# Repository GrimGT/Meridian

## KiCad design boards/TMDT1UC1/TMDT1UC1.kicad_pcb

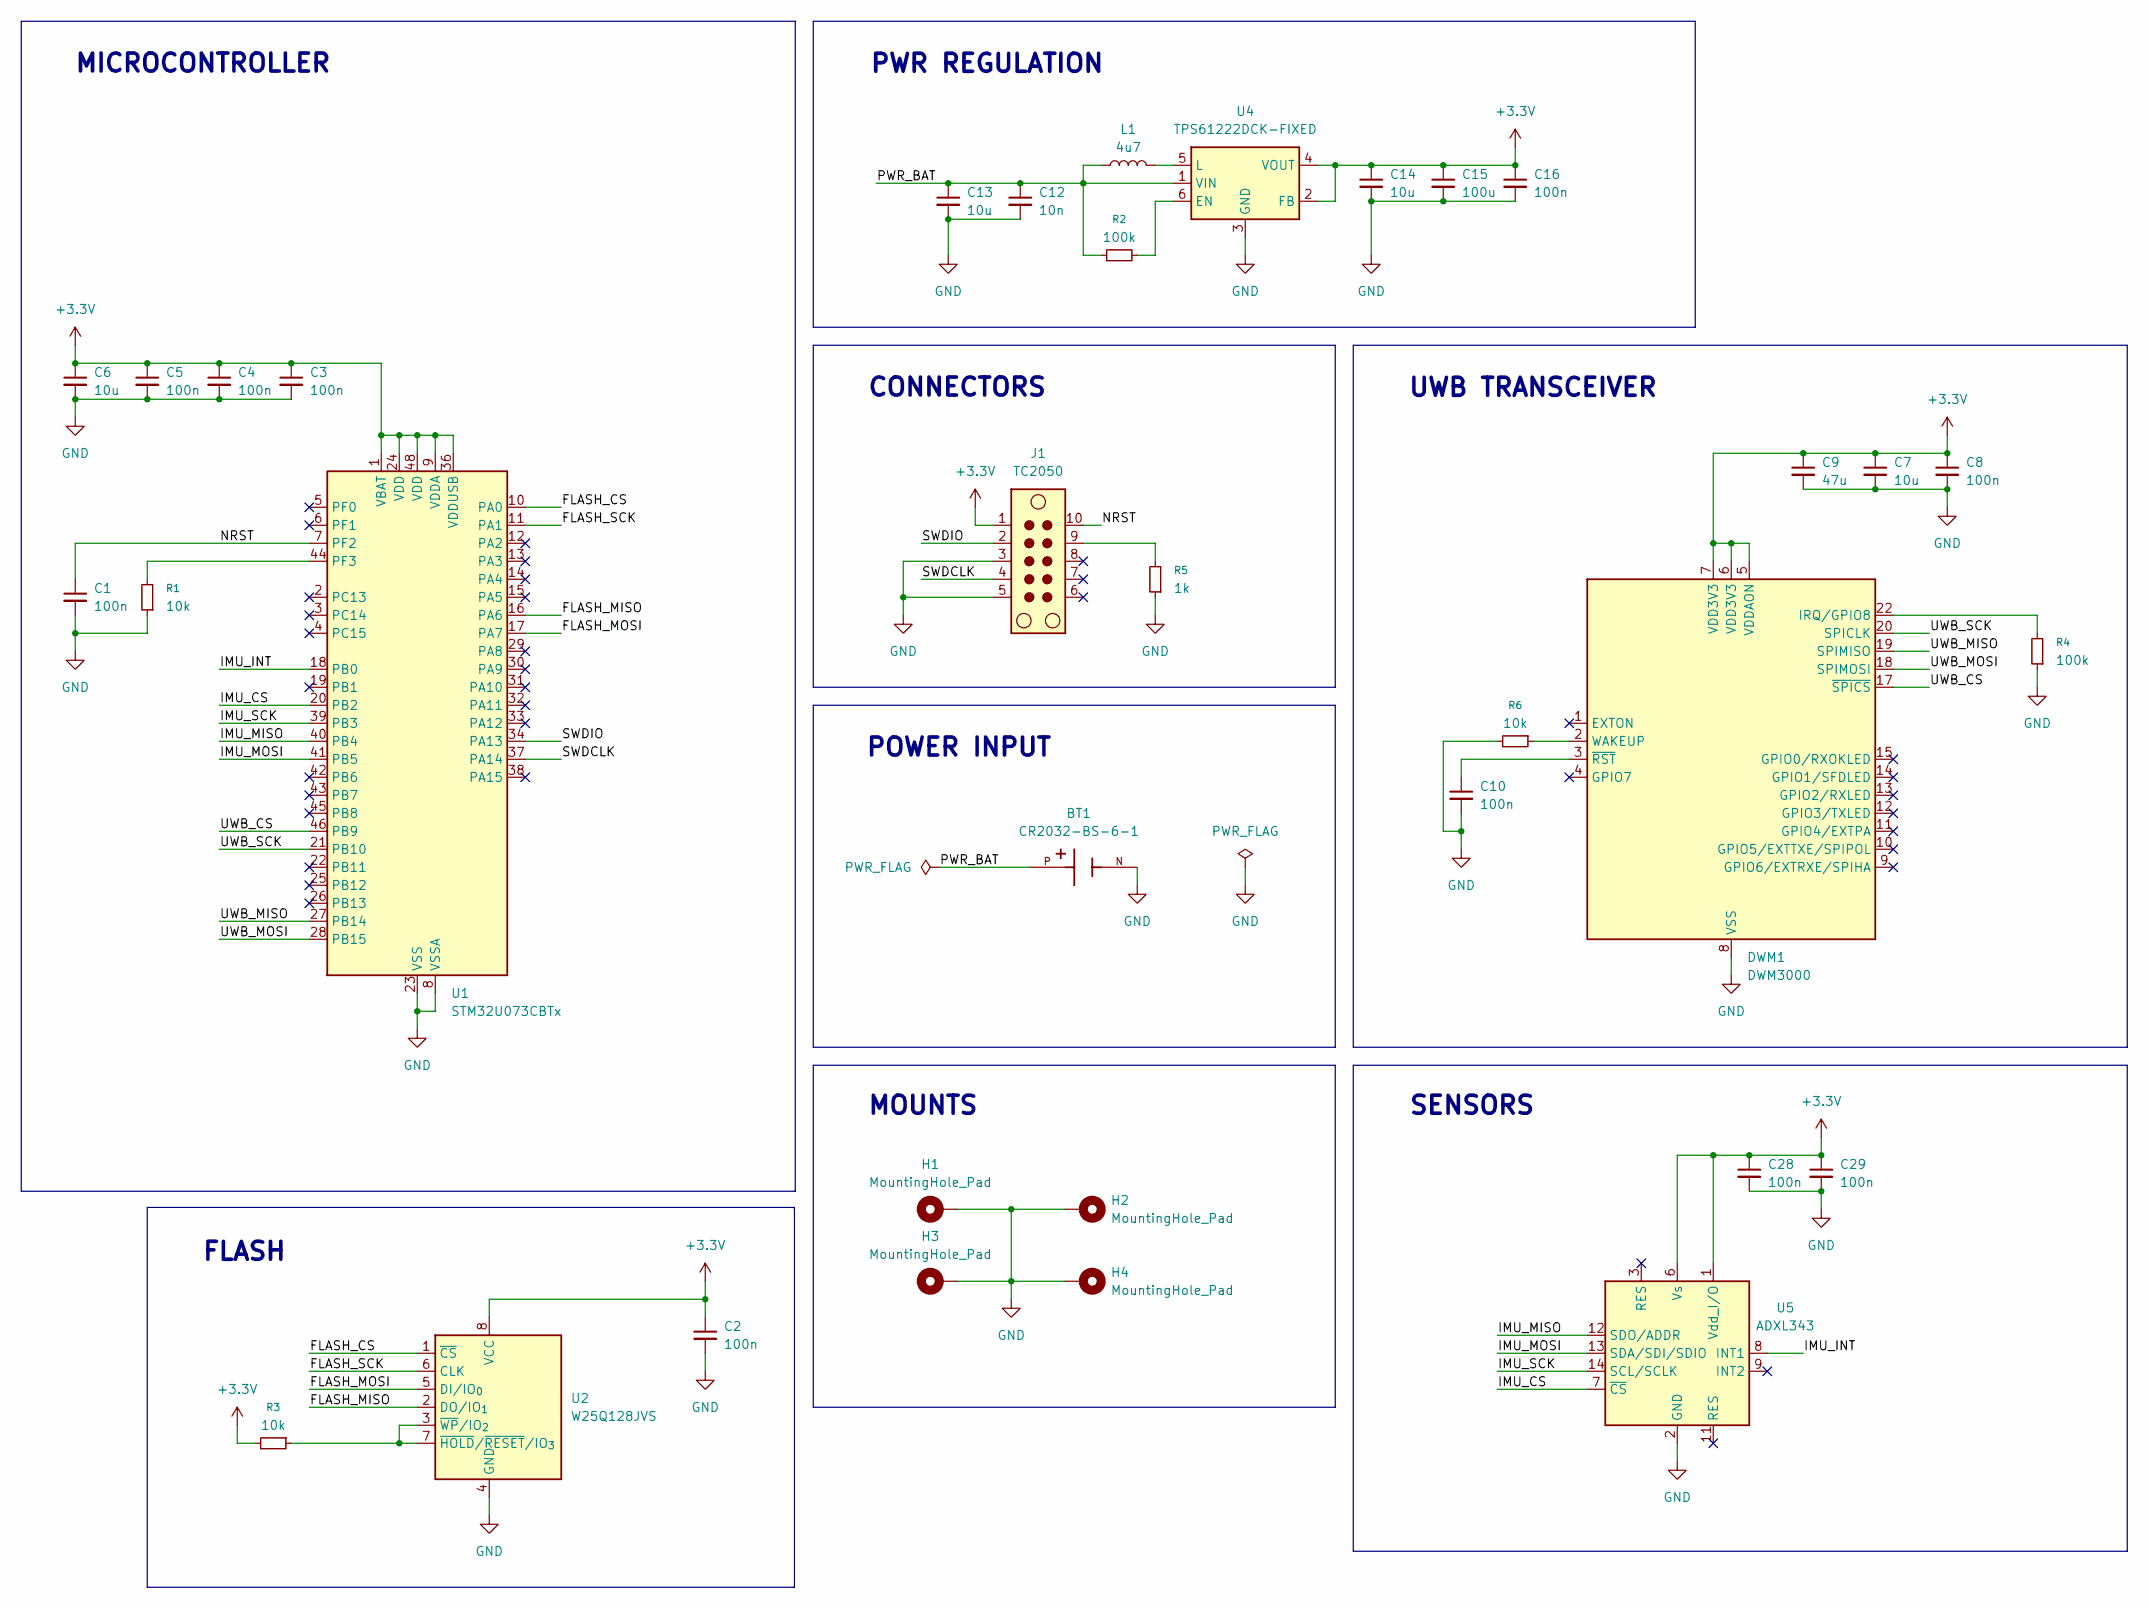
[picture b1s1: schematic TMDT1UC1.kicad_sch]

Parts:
BT1: CR2032-BS-6-1; BAT_CR2032-BS-6-1; PARTREV 2011/2/14
C1, C2, C3, C4, C5, C8, C10, C16, C28, C29: 100n; C_0402_1005Metric
C6, C7, C13, C14: 10u; C_0603_1608Metric
C9: 47u; C_0603_1608Metric
C12: 10n; C_0402_1005Metric
C15: 100u; C_0603_1608Metric
DWM1: DWM3000; DWM1000
H1, H2, H3, H4: MountingHole_Pad; MountingHole_3.2mm_M3_Pad_Via
J1: TC2050; Tag-Connect_TC2050-IDC-NL_2x05_P1.27mm_Vertical
L1: 4u7; L_1210_3225Metric
R1, R3, R6: 10k; R_0402_1005Metric
R2, R4: 100k; R_0402_1005Metric
R5: 1k; R_0402_1005Metric
U1: STM32U073CBTx; LQFP-48_7x7mm_P0.5mm
U2: W25Q128JVS; SOIC-8_5.3x5.3mm_P1.27mm
U4: TPS61222DCK-FIXED; Texas_R-PDSO-G6
U5: ADXL343; LGA-14_3x5mm_P0.8mm_LayoutBorder1x6y

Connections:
+3.3V: C2.1, C3.1, C4.1, C5.1, C6.1, C7.1, C8.1, C9.1, C14.1, C15.1, C16.1, C28.1, C29.1, DWM1.5 (VDDAON), DWM1.6 (VDD3V3), DWM1.7 (VDD3V3), J1.1, R3.2, U1.1 (VBAT), U1.9 (VDDA), U1.24 (VDD), U1.36 (VDDUSB), U1.48 (VDD), U2.8 (VCC), U4.2 (FB), U4.4 (VOUT), U5.1 (Vdd_I/O), U5.6 (Vs)
/FLASH_CS: U1.10 (PA0), U2.1 (~CS)
/FLASH_MISO: U1.16 (PA6), U2.2 (DO/IO_{1})
/FLASH_MOSI: U1.17 (PA7), U2.5 (DI/IO_{0})
/FLASH_SCK: U1.11 (PA1), U2.6 (CLK)
/IMU_CS: U1.20 (PB2), U5.7 (~CS)
/IMU_INT: U1.18 (PB0), U5.8 (INT1)
/IMU_MISO: U1.40 (PB4), U5.12 (SDO/ADDR)
/IMU_MOSI: U1.41 (PB5), U5.13 (SDA/SDI/SDIO)
/IMU_SCK: U1.39 (PB3), U5.14 (SCL/SCLK)
/NRST: C1.1, J1.10, U1.7 (PF2)
/PWR_BAT: BT1.P, C12.1, C13.1, L1.1, R2.1, U4.1 (VIN)
/SWDCLK: J1.4, U1.37 (PA14)
/SWDIO: J1.2, U1.34 (PA13)
/UWB_CS: DWM1.17 (~SPICS), U1.46 (PB9)
/UWB_MISO: DWM1.19 (SPIMISO), U1.27 (PB14)
/UWB_MOSI: DWM1.18 (SPIMOSI), U1.28 (PB15)
/UWB_SCK: DWM1.20 (SPICLK), U1.21 (PB10)
GND: BT1.N, C1.2, C2.2, C3.2, C4.2, C5.2, C6.2, C7.2, C8.2, C9.2, C10.2, C12.2, C13.2, C14.2, C15.2, C16.2, C28.2, C29.2, DWM1.8 (VSS), DWM1.16 (VSS), DWM1.21 (VSS), DWM1.23 (VSS), DWM1.24 (VSS), H1.1, H2.1, H3.1, H4.1, J1.3, J1.5, R1.1, R4.1, R5.1, R6.2, U1.8 (VSSA), U1.23 (VSS), U1.35 (VSS), U1.47 (VSS), U2.4 (GND), U4.3 (GND), U5.2 (GND), U5.4 (GND), U5.5 (GND)
unnamed: DWM1.22 (IRQ/GPIO8), R4.2
unnamed: DWM1.2 (WAKEUP), R6.1
unnamed: C10.1, DWM1.3 (~RST)
unnamed: J1.9, R5.2
unnamed: R1.2, U1.44 (PF3)
unnamed: R3.1, U2.3 (~WP/IO_{2}), U2.7 (~HOLD/~RESET/IO_{3})
unnamed: R2.2, U4.6 (EN)
unnamed: L1.2, U4.5 (L)

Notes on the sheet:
POWER INPUT
SENSORS
FLASH
MOUNTS
PWR REGULATION
UWB TRANSCEIVER
MICROCONTROLLER
CONNECTORS

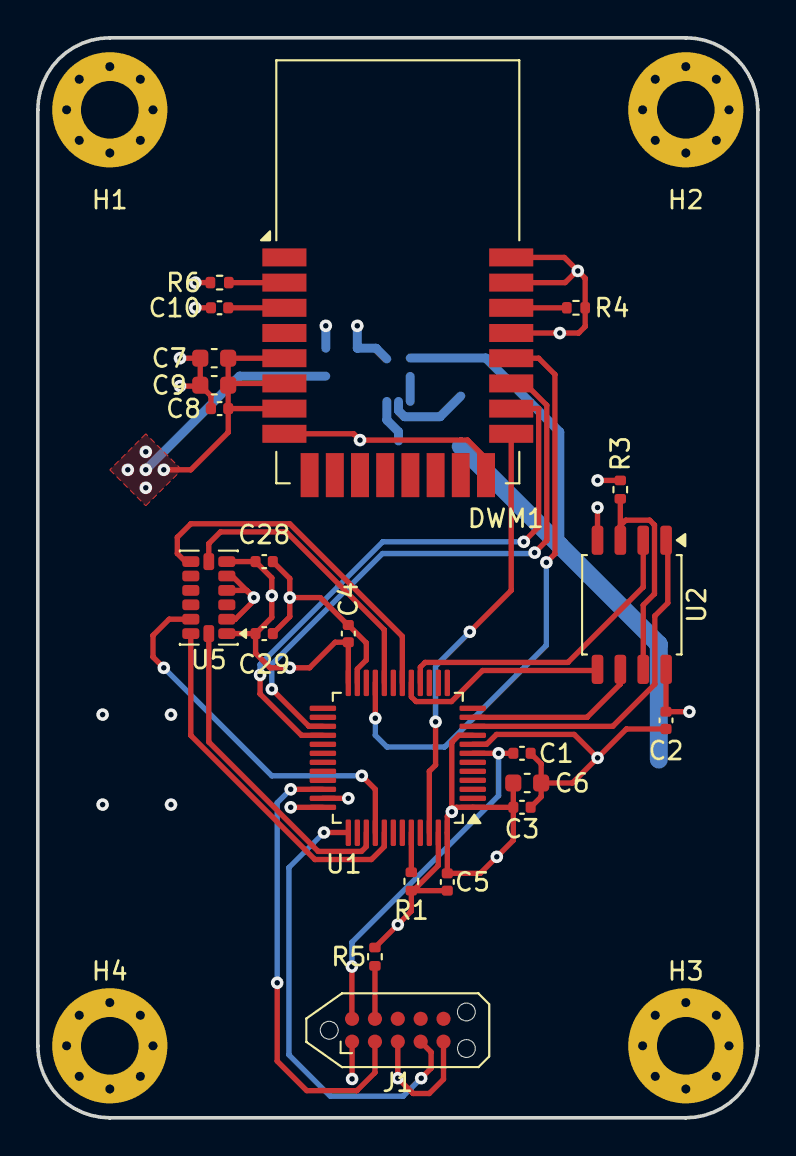
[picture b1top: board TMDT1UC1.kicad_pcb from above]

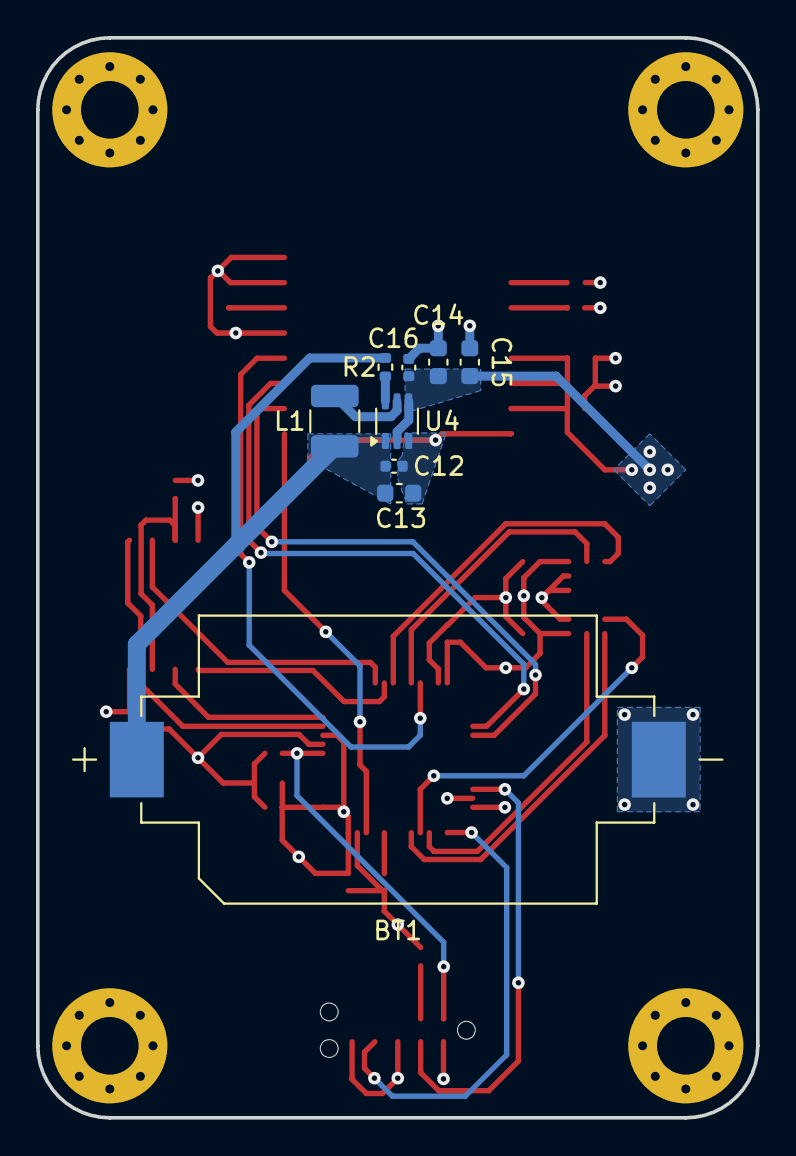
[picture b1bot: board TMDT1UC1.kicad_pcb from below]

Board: 4 copper layers, 40.0 x 60.0 mm, 35 parts (9 on the bottom side), 27 nets.

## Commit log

2026-02-28 Completed base tag schematic (No PCB traces)
2026-02-28 Cleaned up visuals
2026-03-01 Started initial PCB design
2026-03-02 Started switching chips to simpler design on tag (needed factory calibration for reliable TWR)
2026-03-03 Updated PCB (testing auto router)
2026-03-04 Updated board (switched to 4 layer, rerouted cleaner)
